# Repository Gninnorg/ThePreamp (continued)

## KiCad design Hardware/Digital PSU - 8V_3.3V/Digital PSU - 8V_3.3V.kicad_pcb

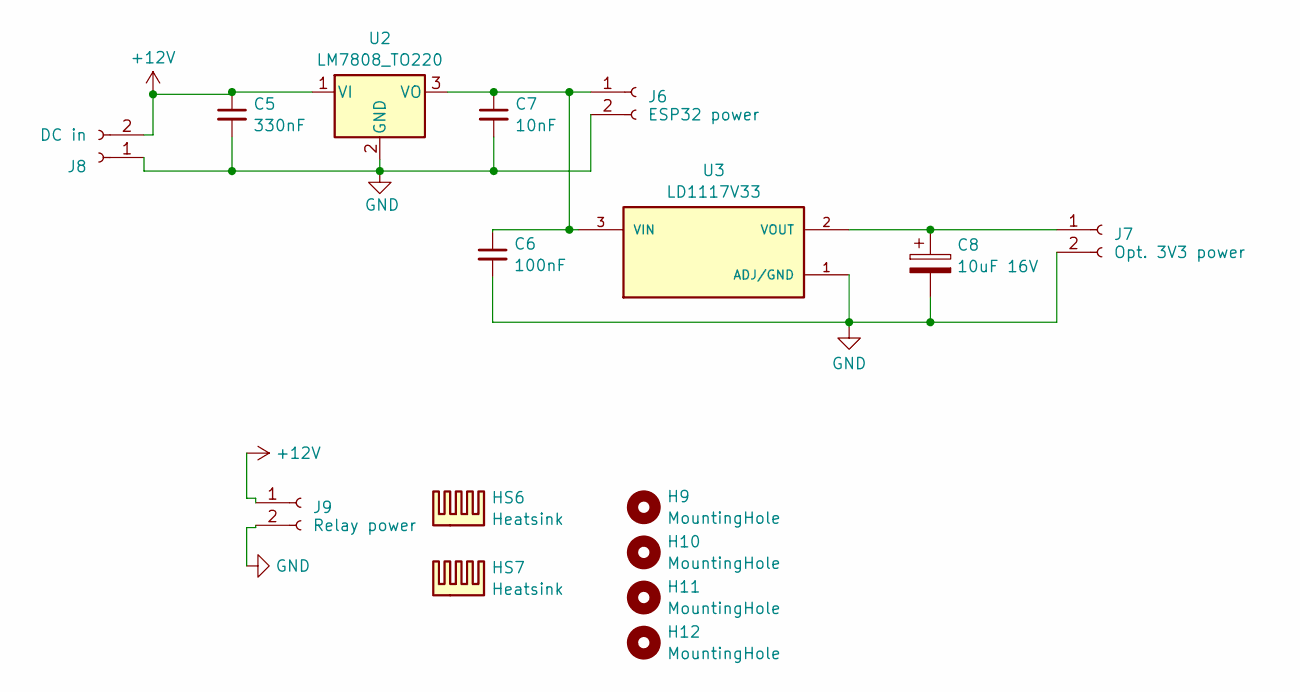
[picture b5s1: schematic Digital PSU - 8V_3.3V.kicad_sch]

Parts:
C5: 330nF; C_0805_2012Metric_Pad1.18x1.45mm_HandSolder
C6: 100nF; C_0805_2012Metric_Pad1.18x1.45mm_HandSolder
C7: 10nF; C_0805_2012Metric_Pad1.18x1.45mm_HandSolder
C8: 10uF 16V; C_1206_3216Metric_Pad1.33x1.80mm_HandSolder
H9, H10, H11, H12: MountingHole; MountingHole_3.2mm_M3_DIN965
HS6, HS7: Heatsink; Heatsink_Fischer_SK145-STS_29x12mm_2xDrill2.5mm
J6: ESP32 power; TBP01R1-508-02BK
J7: Opt. 3V3 power; TBP01R1-508-02BK
J8: DC in; TBP01R1-508-02BK
J9: Relay power; TBP01R1-508-02BK
U2: LM7808_TO220; TO-220-3_Vertical
U3: LD1117V33; TO-220-3_Vertical; PARTREV 37

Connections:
+12V: C5.1, J8.2, J9.1, U2.1 (VI)
GND: C5.2, C6.2, C7.2, C8.2, J6.2, J7.2, J8.1, J9.2, U2.2 (GND), U3.1 (ADJ/GND)
unnamed: C6.1, C7.1, J6.1, U2.3 (VO), U3.3 (VIN)
unnamed: C8.1, J7.1, U3.2 (VOUT)

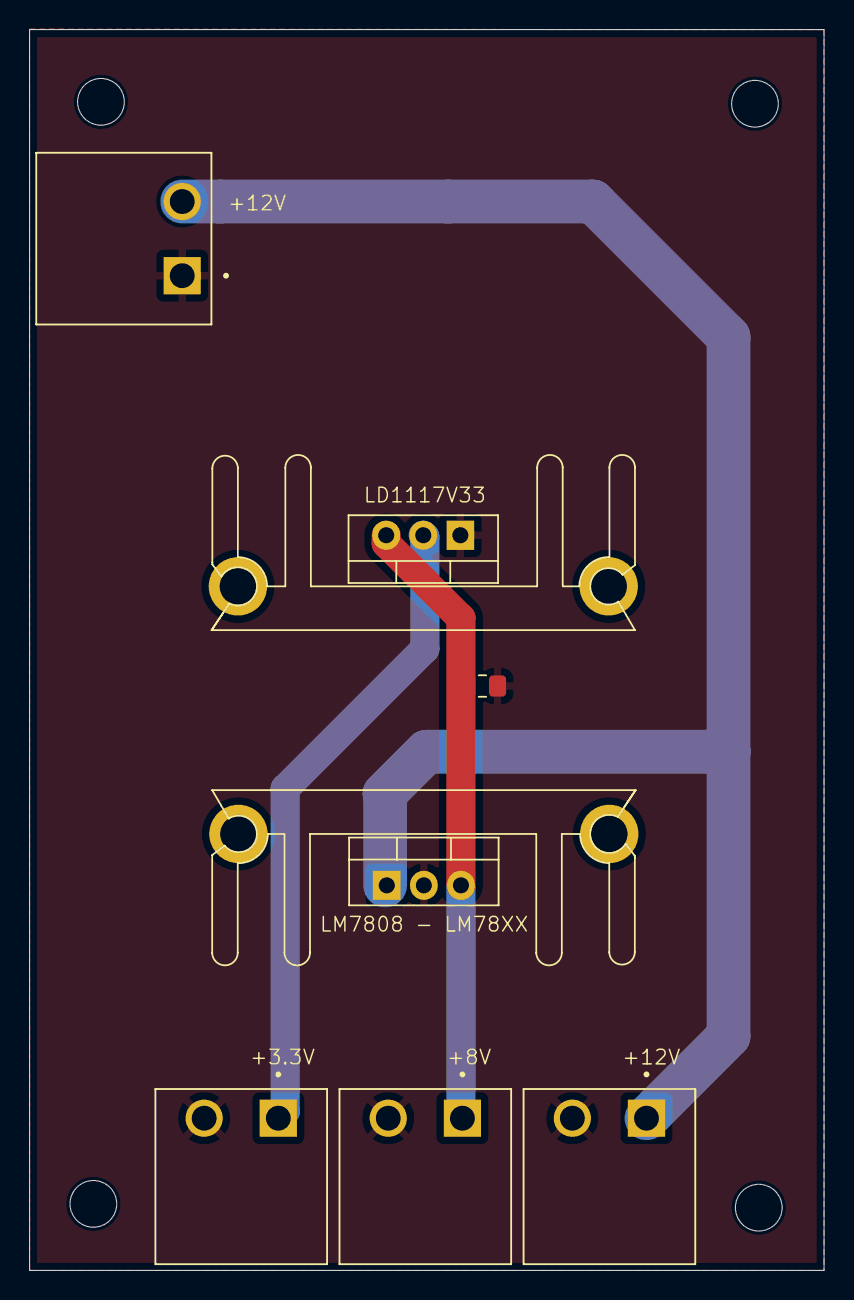
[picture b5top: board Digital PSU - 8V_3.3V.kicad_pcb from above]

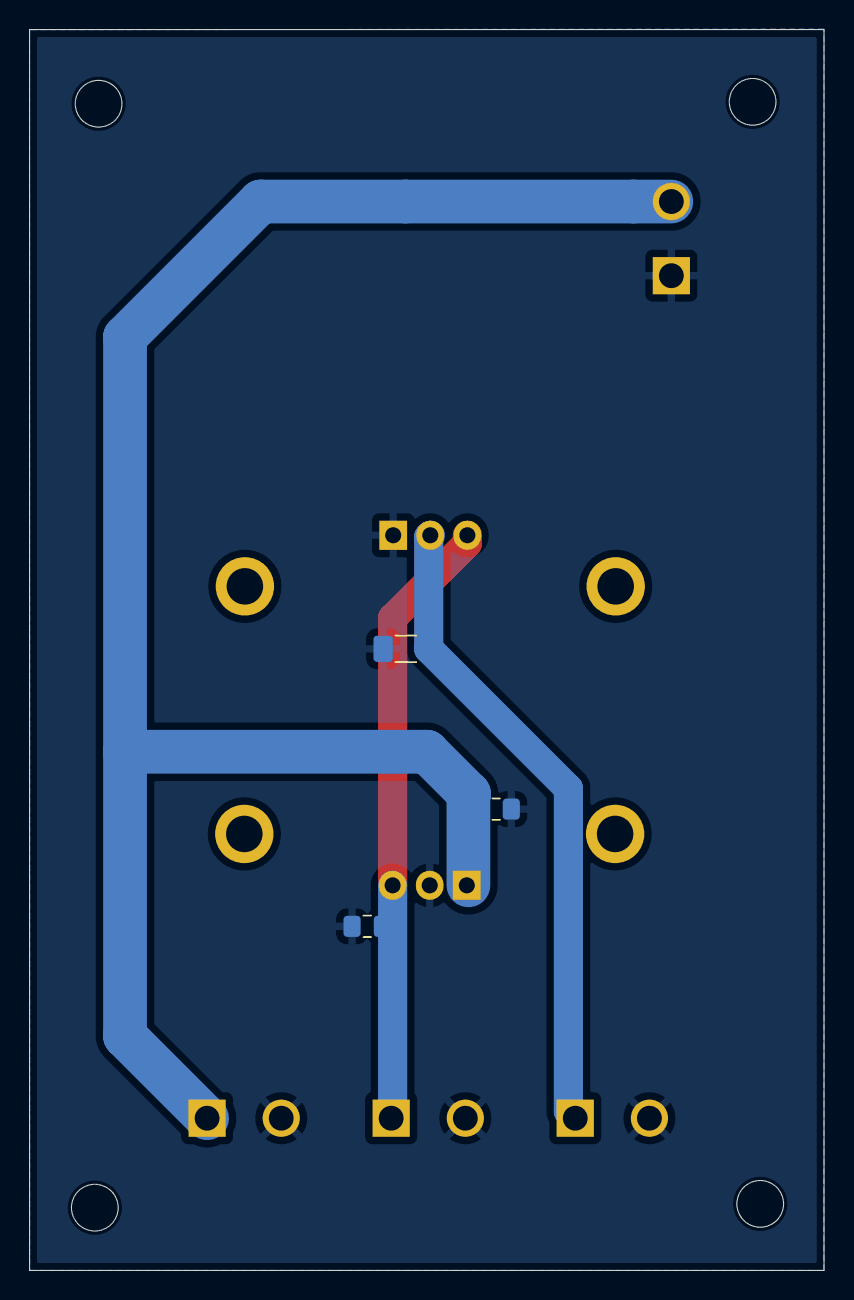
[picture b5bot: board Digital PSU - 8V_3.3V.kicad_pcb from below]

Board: 2 copper layers, 54.4 x 85.0 mm, 16 parts (3 on the bottom side), 4 nets.

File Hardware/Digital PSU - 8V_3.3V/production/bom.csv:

Designator,Footprint,Quantity,Value,LCSC Part #
C5,0805,1,330nF,
C6,0805,1,100nF,
C7,0805,1,10nF,
C8,1206,1,10uF 16V,
"HS6, HS7",Heatsink_Fischer_SK145-STS_29x12mm_2xDrill2.5mm,2,Heatsink,
J6,TBP01R1-508-02BK,1,ESP32 power,
J7,TBP01R1-508-02BK,1,Opt. 3V3 power,
J8,TBP01R1-508-02BK,1,DC in,
J9,TBP01R1-508-02BK,1,Relay power,
U2,TO-220-3_Vertical,1,LM7808_TO220,
U3,TO-220-3_Vertical,1,LD1117V33,

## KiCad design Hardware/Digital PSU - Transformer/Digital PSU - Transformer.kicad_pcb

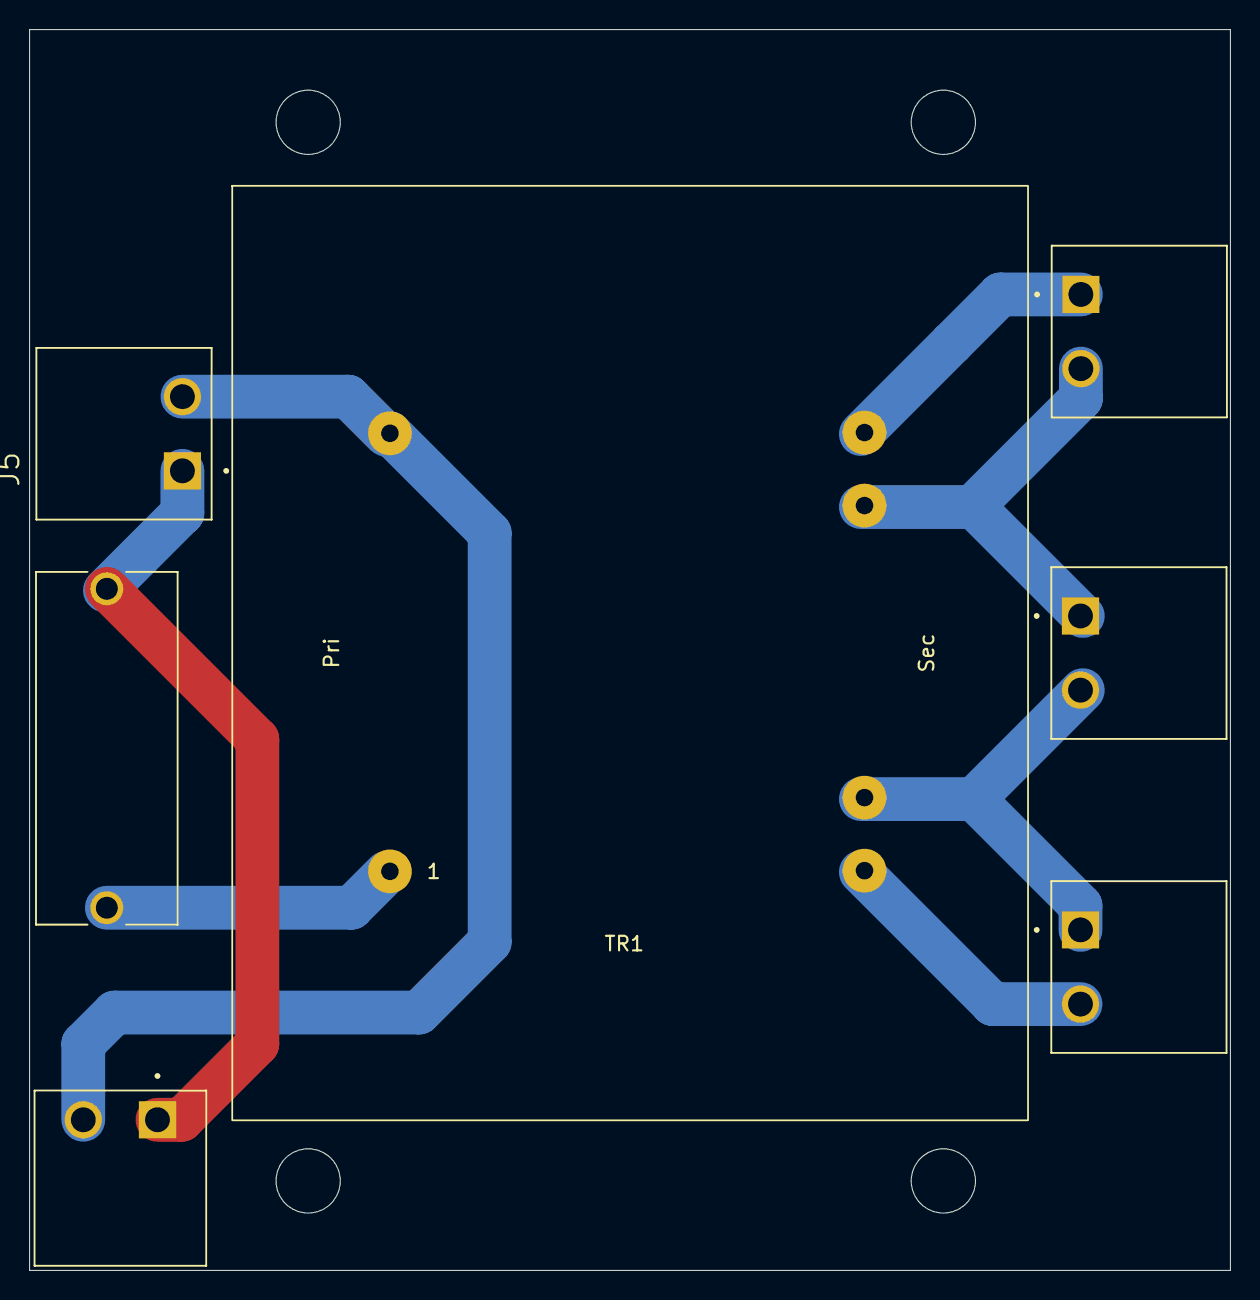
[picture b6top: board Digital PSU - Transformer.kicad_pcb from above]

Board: 2 copper layers, 82.2 x 85.0 mm, 7 parts (0 on the bottom side), 7 nets.

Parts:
F2: Fuse - 8A T; Keystone fuseholder 4527
J1, J5: 230V AC; TBP01R1-508-02BK
J4: 15V AC; TBP01R1-508-02BK
J10, J11: 18V AC; TBP01R1-508-02BK
TR1: Hahn BV EL 603 1027; Transformer_Hahn_BV_EL_603_COMBINED

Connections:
unnamed: F2.2, TR1.1
unnamed: F2.1, J1.1, J5.1
unnamed: J1.2, J5.2, TR1.7
unnamed: J10.1, TR1.8
unnamed: J4.1, J10.2, TR1.9
unnamed: J4.2, J11.1, TR1.13
unnamed: J11.2, TR1.14

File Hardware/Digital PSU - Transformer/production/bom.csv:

Designator,Footprint,Quantity,Value,LCSC Part #
F2,Keystone fuseholder 4527,1,Fuse - 8A T,
"J1, J5",TBP01R1-508-02BK,2,230V AC,
"J10, J11",TBP01R1-508-02BK,2,18V AC,
J4,TBP01R1-508-02BK,1,15V AC,
TR1,Transformer_Hahn_BV_EL_603_COMBINED,1,Hahn BV EL 603 1027,

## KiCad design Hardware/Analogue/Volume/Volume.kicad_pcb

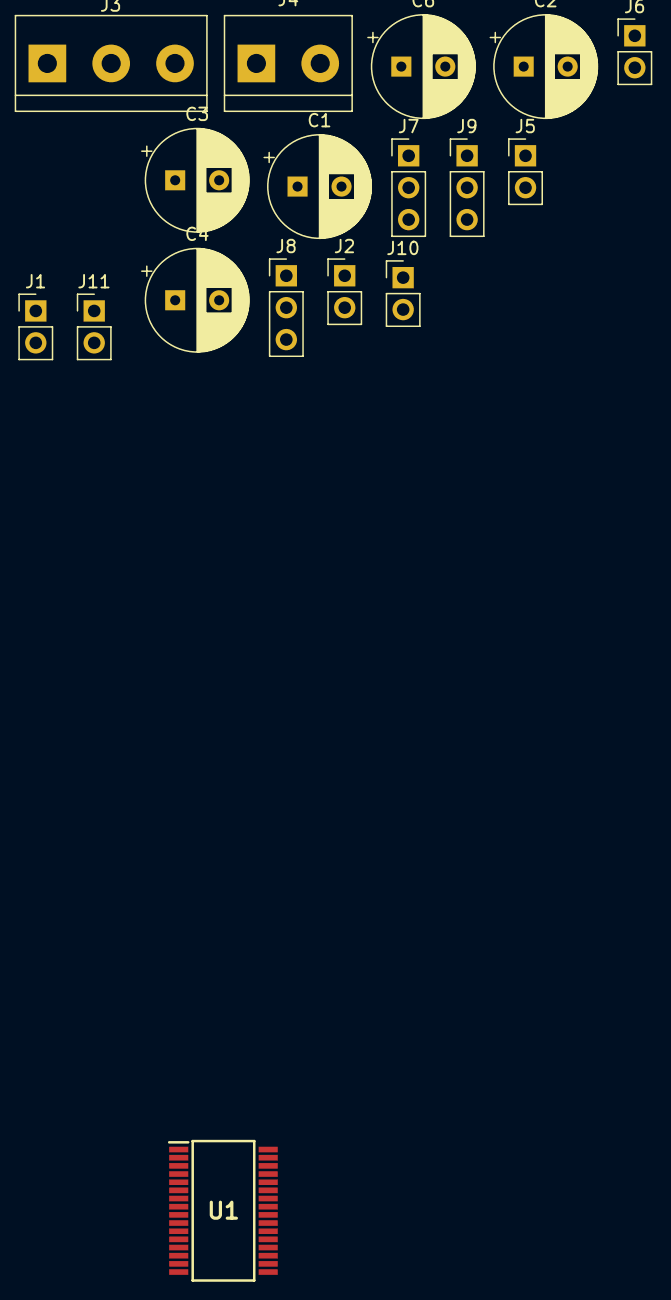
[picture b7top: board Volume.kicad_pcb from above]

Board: 2 copper layers, 17 parts (0 on the bottom side), 14 nets, no tracks yet.

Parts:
C1, C2, C4, C6: 100 uf/25V; CP_Radial_D8.0mm_P3.50mm
C3: 10 uf/50V; CP_Radial_D8.0mm_P3.50mm
J1, J6: Audio In Right; PinHeader_1x02_P2.54mm_Vertical
J2, J5: Audio In Left; PinHeader_1x02_P2.54mm_Vertical
J3: Audio Power; TerminalBlock_bornier-3_P5.08mm
J4: Digital Power; TerminalBlock_bornier-2_P5.08mm
J7: Buffer Power; PinHeader_1x03_P2.54mm_Vertical
J8: Buffer In Left; PinHeader_1x03_P2.54mm_Vertical
J9: Buffer In Right; PinHeader_1x03_P2.54mm_Vertical
J10: Buffer Out Right; PinHeader_1x02_P2.54mm_Vertical
J11: Buffer Out Left; PinHeader_1x02_P2.54mm_Vertical
U1: Muses_72323; SOP65P760X145-32N

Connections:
+15V: C1.1, J3.1, J7.1, U1.21 (D_V+), U1.23 (AR_V+), U1.24 (AL_V+)
-15V: C2.2, J3.3, J7.3, U1.25 (AR_V-), U1.26 (AL_V-), U1.28 (D_V-)
Audio L buffer: J2.1, U1.27 (INL)
Audio R buffer: J1.1, U1.22 (INR)
GND: C1.2, C2.1, C3.2, C4.2, C6.2, J1.2, J2.2, J3.2, J4.2, J5.2, J6.2, J7.2, J10.2, J11.2, U1.1 (NC), U1.5 (L_REF), U1.7 (L_REF), U1.8 (L_REF), U1.9 (R_REF), U1.10 (R_REF), U1.12 (R_REF), U1.30 (ADR0), U1.31 (ADR1), U1.32 (D_REF)
L+: J8.3, U1.6 (L+)
L-: J8.2, U1.4 (L-)
unnamed: C3.1, U1.29 (D_CAP)
unnamed: C4.1, U1.2 (L_CAP)
unnamed: C6.1, U1.15 (R_CAP)
OUTL: J8.1, U1.3 (OUTL)
OUTR: J9.1, U1.14 (OUTR)
R+: J9.3, U1.11 (R+)
R-: J9.2, U1.13 (R-)

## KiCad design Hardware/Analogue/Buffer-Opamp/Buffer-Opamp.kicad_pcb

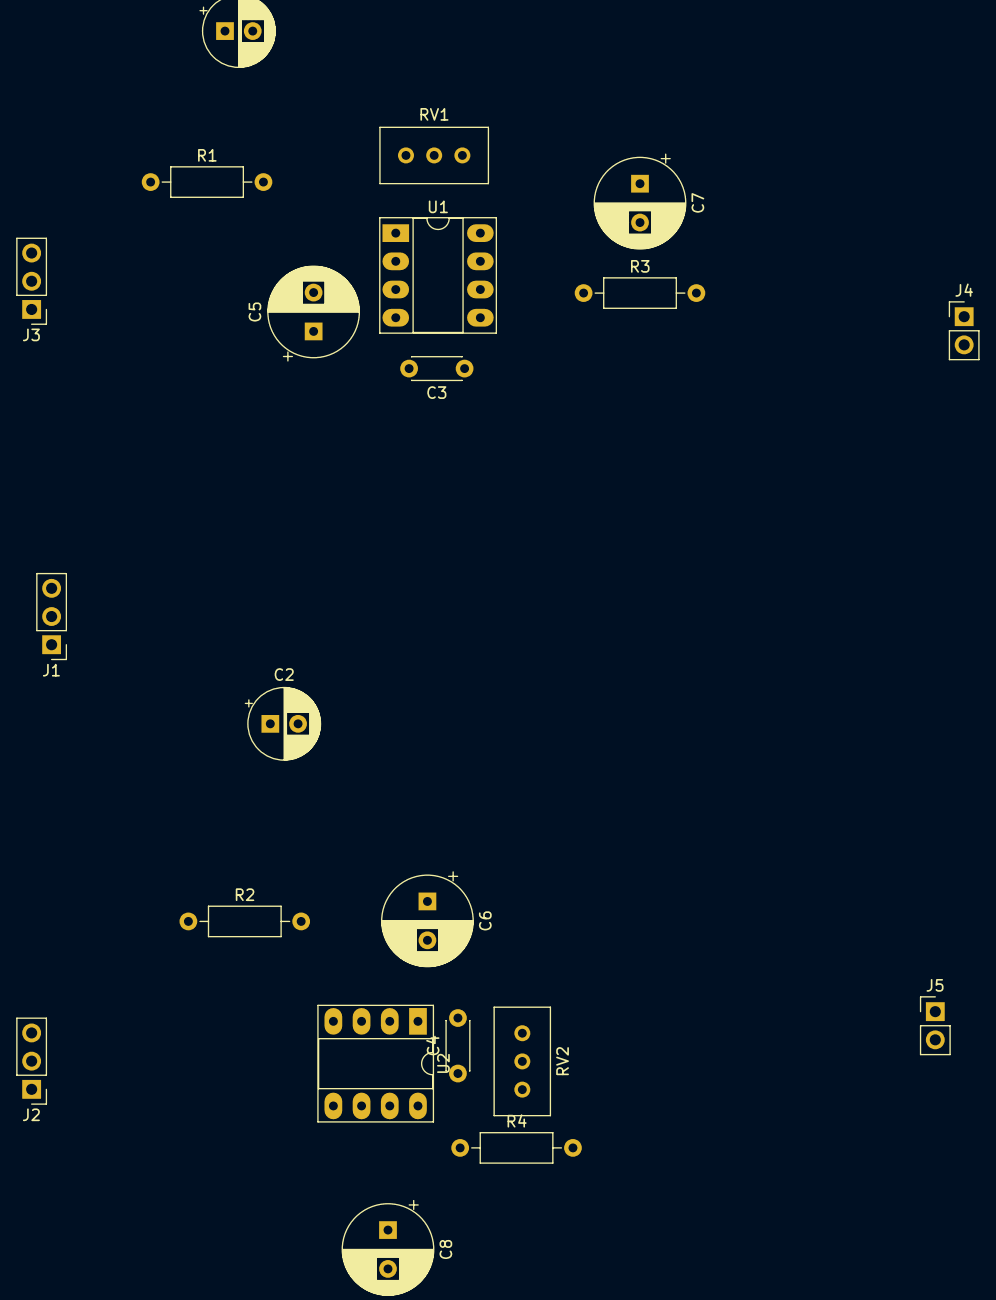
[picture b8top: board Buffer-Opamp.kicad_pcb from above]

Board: 2 copper layers, 21 parts (0 on the bottom side), 17 nets, no tracks yet.

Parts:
C1, C2: 10 uF; CP_Radial_D6.3mm_P2.50mm
C3, C4: 10 pF; C_Disc_D4.3mm_W1.9mm_P5.00mm
C5, C6, C7, C8: 100 uf/25V; CP_Radial_D8.0mm_P3.50mm
J1, J2, J3: Conn_01x03_Female; PinHeader_1x03_P2.54mm_Vertical
J4, J5: Conn_01x02_Female; PinHeader_1x02_P2.54mm_Vertical
R1, R2: 100K; R_Axial_DIN0207_L6.3mm_D2.5mm_P10.16mm_Horizontal
R3, R4: 47; R_Axial_DIN0207_L6.3mm_D2.5mm_P10.16mm_Horizontal
RV1, RV2: 100k; Potentiometer_Bourns_3296W_Vertical
U1, U2: NE5534; DIP-8_W7.62mm_Socket_LongPads

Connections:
+15V: C7.1, C8.1, J1.1, RV1.2, RV2.2, U1.7 (V+), U2.7 (V+)
-15V: C5.2, C6.2, J1.3, U1.4 (V-), U2.4 (V-)
GND: C5.1, C6.1, C7.2, C8.2, J1.2, J4.2, J5.2, R1.1, R2.1
L+: C2.1, J2.3
L-: C4.2, J2.2, U2.2 (-)
unnamed: C1.2, R1.2, U1.3 (+)
unnamed: C2.2, R2.2, U2.3 (+)
unnamed: J4.1, R3.2
unnamed: J5.1, R4.2
unnamed: RV1.1, U1.8 (C/B)
unnamed: RV1.3, U1.1 (BAL)
unnamed: RV2.1, U2.8 (C/B)
unnamed: RV2.3, U2.1 (BAL)
OUTL: C4.1, J2.1, R4.1, U2.6
OUTR: C3.1, J3.1, R3.1, U1.6
R+: C1.1, J3.3
R-: C3.2, J3.2, U1.2 (-)

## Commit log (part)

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2023-05-10 Initial pcb design
2023-05-10 Clean up directories
2023-05-10 schematic initial draft
2023-06-08 Added libraries for 72320 and 72323
2023-08-12 added footprint to rca connector
2023-08-16 Added input section
2023-09-27 added muses72323
2023-10-11 ADD ANALOG PART
2023-10-26 seperate kicad project for buffer
2023-11-22 analogue pcb work
2023-11-29 update analogue schematic
2023-12-20 rca pcb layout v.0.8
2024-01-17 more pcb layout
2024-01-17 KiCad 7 and updated pcb
2024-01-21 Cleanup
2024-01-24 pcb redesign
2024-01-27 Added Trigger functionality (12V and switch)
2024-01-28 Added +12V to COM on ULN2803 (common fly back diode)
2024-01-31 Final version?
2024-02-03 Added KiCad template for daughter board(s)
2024-02-03 Added template for daughter board
2024-02-03 Controller pcb dimensions added
2024-02-04 Displays changed to SPI
2024-02-04 Test code for two displays
2024-02-04 Pins updated
2024-02-04 Add power relay control output
2024-02-06 Added symbol/footprint for display
2024-02-11 Controller pcb is ready (except for connectors)
2024-02-12 Moved digital connector to match analog pcb
2024-02-14 Silk screens added
2024-02-17 v1.1 - added internal input and IDC for switches etc
2024-02-18 Changed switch connector to 1 row
2024-02-18 Silkscreen updates
2024-02-18 16 pin IDC connector added for digital control input (GND interleaved)
2024-02-25 Digital connector (IDC 16) aligned on controller and analog board
2024-02-26 Added optional M8 connectors for switches, 12V triggers and analog measurements
2024-02-27 Changed power connectors
2024-02-28 Added 3D-files for connectors
2024-03-02 Ready for production
2024-03-03 Ready for review before production
2024-03-05 Started work on digital psu
2024-03-06 More work on PSU
2024-03-08 Removed +/-15V connector from analog board
2024-03-10 Updated Template-Daughter-board to reflect changes
2024-03-11 Display logo
2024-03-13 Connector placement in chassis
2024-03-16 Added transformer for Digital PSU
2024-03-16 Minor updates
2024-03-17 Added LD1117V33 to digital psu
2024-03-17 Measurements of chassis added
2024-03-17 Added analog pcb in right position on chassis drawing
2024-03-18 chassis
2024-03-18 Aligned IDC connector placement between controller and analog pcb
2024-03-21 Pcb dimensions
2024-03-23 Chassis placement new draft
2024-03-24 Chassis placement draft
2024-03-26 Small adjustments to draft
2024-03-26 pcb splitout
2024-03-26 Exclude backup directories
2024-03-26 gitignore test
2024-04-03 Updated pcb 3.3V + adjust of connectors on controller pcb
2024-04-10 Moved connector on Analogue pcb
2024-04-14 Ready for review (updated Digital PSU - Transformer and Controller)
2024-04-25 Ready for review
2024-05-19 Last changes before ordering of pcb
2024-05-29 Test code
2024-05-29 Updated to do
2024-06-08 Fixed display issue on start, changed IR lib
2024-06-10 Very first MVP version
2024-06-13 MVP version - stabilized displays
2024-09-04 Separating digital and analog ground
2024-09-12 daughter board muses + buffer
2024-09-19 PCB Daughter board started
2024-09-26 started pcb tracks
2024-10-03 almost there with pcb again
2024-10-24 pcb update
2024-10-25 Footprints updated - rerouting still missing
2024-10-26 PCB ready for review
2024-10-31 Small adjustments ready to order.
2024-11-29 Muses72323 added + input selection fixed
2024-12-09 Volume (attenuation has been fixed)
2024-12-16 Input and volume display fonts
2024-12-19 Minor changes
2024-12-19 WiFi + OTA
2024-12-22 Added support for captive portal
2024-12-29 Added display of wifi QR
2024-12-29 Added image files
2024-12-30 QR code displays ok - but AP closes down to fast
2024-12-30 Manual sync
    Manual sync
2025-01-02 AP Optimizations
2025-01-04 Added wifi signal strength display
2025-01-04 Adjustment to wifi signal display
2025-01-04 Adjusted wifi strength scale
2025-01-05 Code cleanup
2025-01-05 More cleanup
2025-01-09 Fix of input name, volumesteps.
2025-01-13 Function created for temperature display (empty)
2025-01-13 Merged with main
2025-01-16 Add temperature read from ads1115
2025-01-16 merged branch something
2025-01-16 added comment
2025-01-16 added comment line
2025-01-16 Comments
2025-01-20 Added visualization of temperatures
2025-02-06 small changes
2025-02-10 Added debug messages
2025-02-11 Debugging of rotary encoders
2025-02-13 Added pullup resistors on D34-35 on controller pcb
2025-03-06 After update to Kicad 9
2025-03-06 pcb bug output relay fixed - when off output should be shorted to ground a
2025-03-27 Changed vol display to steps
2025-04-09 Lowered SPI bus to 500kHz for Muses
2025-04-13 Delay Muses72323 start (wait until wifi start up)
2025-04-21 Fixed startup calls to setVolume
2025-04-21 Added preset IR codes (ScanSonic remote)
2025-05-03 Webserial added and working
2025-05-08 Various changes and todos done
2025-05-21 Added support for simple WebSerial commands
2025-05-21 Added function to export settings as json
2025-05-25 add support to list setting via webserial (not tested)
2025-09-14 REfactoring - move image data for logo and QR code to separate files
2026-02-07 Stabilize display init - local Muses lib
2026-02-15 Fixed output relay wiring on analog board schematic & pcb
2026-02-25 Added 10uF for EN pin to stabilize init of displays
